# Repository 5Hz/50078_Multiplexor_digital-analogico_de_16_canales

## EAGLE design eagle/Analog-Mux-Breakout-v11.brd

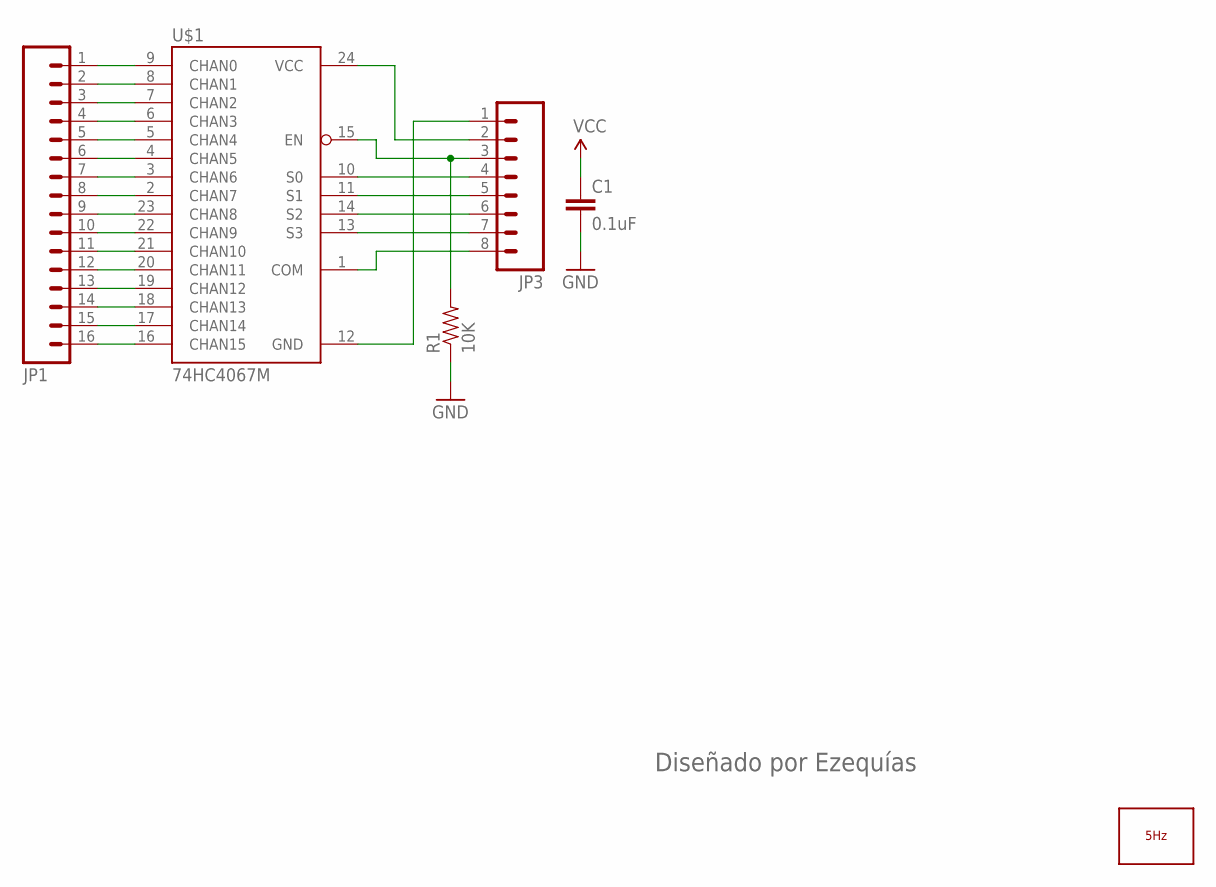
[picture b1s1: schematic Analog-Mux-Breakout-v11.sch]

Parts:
C1: 0.1uF; C0402
JP1: M16PTH; 1X16
JP3: M08; 1X08
LOGO1: LOGO_5HZ_H_10MM; 5HZ_LOGO_H_10MM
R1: 10K; C0402
U$1: 74HC4067M; SOIC_28

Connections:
C0: JP1.1, U$1.9 (CHAN0)
C1: JP1.2, U$1.8 (CHAN1)
C2: JP1.3, U$1.7 (CHAN2)
C3: JP1.4, U$1.6 (CHAN3)
C4: JP1.5, U$1.5 (CHAN4)
C5: JP1.6, U$1.4 (CHAN5)
C6: JP1.7, U$1.3 (CHAN6)
C7: JP1.8, U$1.2 (CHAN7)
C8: JP1.9, U$1.23 (CHAN8)
C9: JP1.10, U$1.22 (CHAN9)
C10: JP1.11, U$1.21 (CHAN10)
C11: JP1.12, U$1.20 (CHAN11)
C12: JP1.13, U$1.19 (CHAN12)
C13: JP1.14, U$1.18 (CHAN13)
C14: JP1.15, U$1.17 (CHAN14)
C15: JP1.16, U$1.16 (CHAN15)
EN: JP3.3, R1.2, U$1.15 (EN)
GND: C1.2, JP3.1, R1.1, U$1.12 (GND)
S0: JP3.4, U$1.10 (S0)
S1: JP3.5, U$1.11 (S1)
S2: JP3.6, U$1.14 (S2)
S3: JP3.7, U$1.13 (S3)
SIG: JP3.8, U$1.1 (COM)
VCC: C1.1, JP3.2, U$1.24 (VCC)

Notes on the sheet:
Diseñado por Ezequías

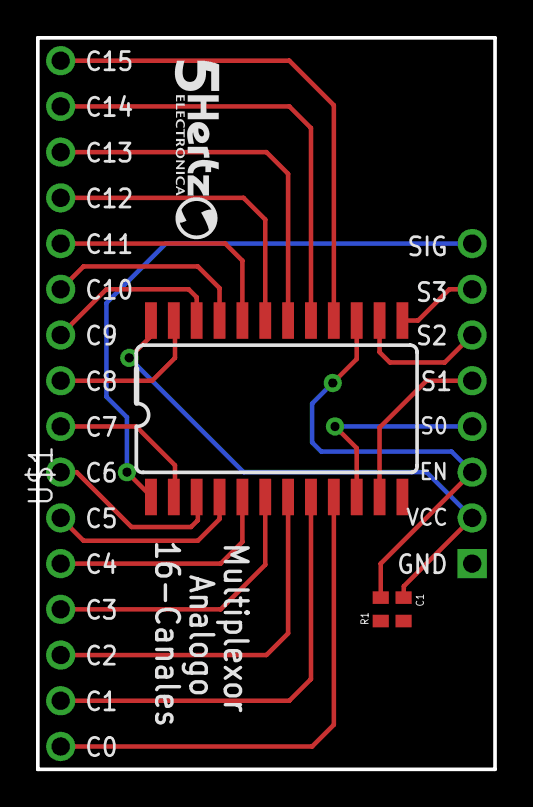
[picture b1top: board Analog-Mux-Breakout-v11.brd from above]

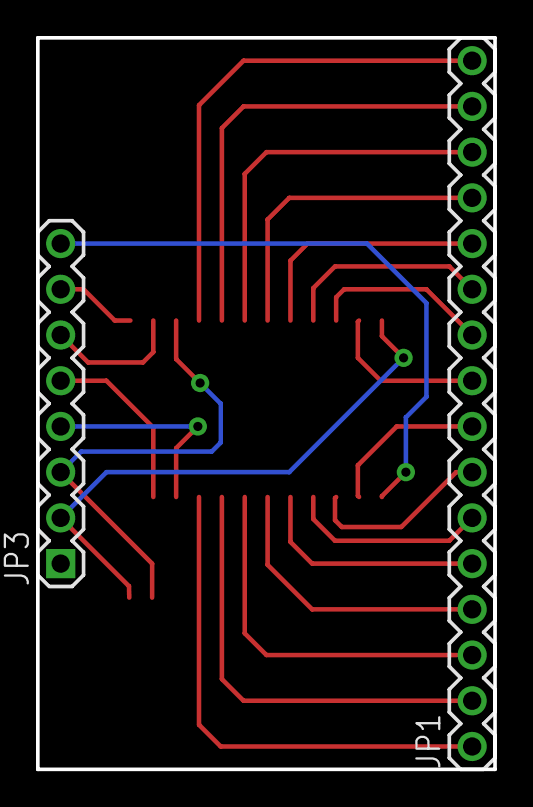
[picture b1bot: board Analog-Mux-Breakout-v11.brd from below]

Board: 2 copper layers, 25.4 x 40.6 mm, 6 parts (2 on the bottom side), 24 nets.

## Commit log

2014-01-13 creación
